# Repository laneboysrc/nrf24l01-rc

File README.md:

# nRF24-based RC car receiver, compatible with HobbyKing HK310 and Turnigy 3XS

This project includes **electronics** and **firmware** to build **surface RC receivers** that can replace the HobbyKing [HKR3000](http://hobbyking.com/hobbyking/store/__12187__HK_3000_3ch_2_4ghz_FHSS_RX_suit_the_HK310_Transmitter.html) and [XR3100](http://hobbyking.com/hobbyking/store/__22910__HK3100_3ch_2_4ghz_FHSS_Micro_RX_suits_HK310_Turnigy_3XS_TX_.html) receivers. They can be used with the [HK300](http://hobbyking.com/hobbyking/store/__12177__HK_300_3_Channel_2_4ghz_FHSS_Ground_Radio.html), [HK310](http://hobbyking.com/hobbyking/store/__12181__HK_310_3_Channel_2_4ghz_FHSS_Ground_Radio.html) and [Turnigy 3XS](http://hobbyking.com/hobbyking/store/__24905__Turnigy_3XS_FHSS_2_4GHz_3_Channel_Radio_System.html) RC car radio systems.

The receivers make use of off-the-shelf inexpensive RF modules.

Two variants are provided:

- [lpc812-nrf24l01](lpc812-nrf24l01-receiver/): NRF24L01+ module plus a [NXP LPC812](http://www.nxp.com/products/microcontrollers/cortex_m0_m0/series/LPC800.html) MCU
- [nrf24le1](nrf24le1-receiver/): Using a NRF24LE1 module (integrated 8051 MCU)

Technical information about the inner working of the receivers can be found
in **[hkr3000-info.md](doc/hkr3000-info.md)**.

## Advantages of the NRF24L01+ - LPC812 version

- Easily obtainable and very low cost NRF module (less than USD 1 including shipping in qty 10 on eBay, Aliexpress)
- Very precise servo pulses due to LPC812 timer hardware
- ARM Cortex-M0 32-bit CPU is easy to program for with the GCC ARM compiler
- No proprietary programmer required as the MCU has a ROM bootloader that can be flashed with an  USB-to-serial dongle
- Servo pulses can be updated down to every 5 ms (200 Hz). In theory this may provide better response but in practice the transmitter would need to be modified to fully take
advantage of this fact.
- UART output using the LANE Boys RC [preprocessor protocol](http://laneboysrc.blogspot.com/2012/12/pre-processor-for-diy-rc-light.html), e.g. to hook up the [DIY RC light controller](https://github.com/laneboysrc/rc-light-controller) with a single servo cable.

Downsides:

- Requires a PCB and intermediate SMD soldering skills
- No CPPM output (but it has a UART output that can carry CPPM-like data and more)

## Advantages of the NRF24LE1 version

- Low part count: NRF24LE1 module, voltage regulator, a few capacitors; done!
- Simple to build even on a breadboard
- CPPM output
- UART output using the LANE Boys RC [preprocessor protocol](http://laneboysrc.blogspot.com/2012/12/pre-processor-for-diy-rc-light.html), e.g. to hook up the [DIY RC light controller](https://github.com/laneboysrc/rc-light-controller) with a single servo cable. Baudrate is limited to 38400 though.

Downsides:

- NRF24LE1 module is more expensive than NRF24L01 and harder to find
- Requires special programming hardware. Multiple open-source versions can be found on the Internet.
- Servo pulses are software timed, hence slightly jittery despite using interrupts. Note that the firmware included in this project is improved over the original HKR3000 and XR3100 firmware, which regularly extends servo pulses by 16 us due to poor interrupt logic implementation.
- For the PCB provided in this project you need to get the NRF24LE1 module version that has an SMD crystal (size 21 x 15 mm)

The NRF24LE1 firmware included in this project can be compiled to be compatible with the HKR3000 and XR3100 hardware. However, since those receivers use the OTP version (NRF24LE1G) one would have to replace the chip with the NR24LE1E versions to be able to use it.

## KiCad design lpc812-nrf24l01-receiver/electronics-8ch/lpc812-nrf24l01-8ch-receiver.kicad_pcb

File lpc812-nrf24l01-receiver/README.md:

The LPC812-based receiver comes in two variants:

3/4 channel version
- Supports the original HobbyKing HK310 protocol
- Supports the LANE Boys RC 4 channel protocol
- Based on 16 pin TSSOP LPC812
- Uses the cheap nRF24 modules with the 2x4 pinheader

8 channel version
- Supports the original HobbyKing HK310 protocol
- Supports the LANE Boys RC 4 channel protocol
- Supports the LANE Boys RC 8 channel protocol
- Based on 20 pin TSSOP LPC812
- Uses a different, smaller nRF24L01 module that comes variants
with PCB antenna and IPX connector

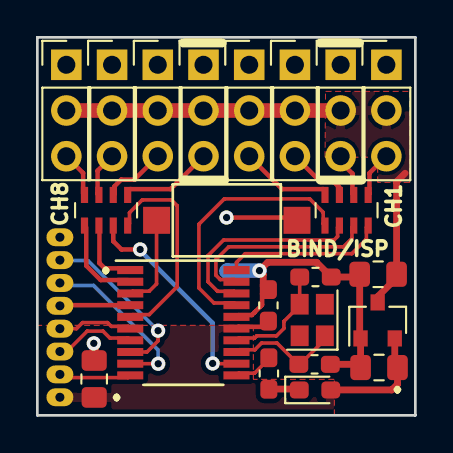
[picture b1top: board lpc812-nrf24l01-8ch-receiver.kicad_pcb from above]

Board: 2 copper layers, 21.0 x 21.0 mm, 23 parts (1 on the bottom side), 30 nets.

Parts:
C1: 1u/16V; C_0805_2012Metric_Pad1.15x1.40mm_HandSolder
C3, C5: 47u/6.3V; C_0805_2012Metric_Pad1.15x1.40mm_HandSolder
C4: 100n; C_0603_1608Metric_Pad1.05x0.95mm_HandSolder
C6, C7: 18p; C_0603_1608Metric_Pad1.05x0.95mm_HandSolder
D1: LED; LED_0603_1608Metric_Pad1.05x0.95mm_HandSolder
J1: CH1; PinHeader_1x03_P2.54mm_Vertical
J2: CH2/Rx; PinHeader_1x03_P2.54mm_Vertical
J3: CH3; PinHeader_1x03_P2.54mm_Vertical
J4: CH4; PinHeader_1x03_P2.54mm_Vertical
J5: CH5/Tx; PinHeader_1x03_P2.54mm_Vertical
J6: CH6; PinHeader_1x03_P2.54mm_Vertical
J7: CH7; PinHeader_1x03_P2.54mm_Vertical
J8: CH8; PinHeader_1x03_P2.54mm_Vertical
R1: 270; R_0603_1608Metric_Pad1.05x0.95mm_HandSolder
RN1, RN2: 1k x 4; R_Array_Concave_4x0603
SW1: BIND/ISP; Tact switch 6x4x3
U1: MCP1703A-3302_SOT23; SOT-23
U2: LPC812M101JDH20; TSSOP-20_4.4x6.5mm_P0.65mm
U3: NRF24L01_E01_ML01; nrf24l01-E01-ML01IPX
Y1: 12MHz; Crystal_SMD_2520-4Pin_2.5x2.0mm

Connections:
/BIND-ISP: SW1.1, U2.3
/CE: U2.10, U3.2
/CH1: RN1.4, U2.20
/CH2-Rx: RN1.3, U2.19
/CH3: RN1.2, U2.18
/CH4: RN1.1, U2.17
/CH5-Tx: RN2.4, U2.5
/CH6: RN2.3, U2.12
/CH7: RN2.2, U2.1
/CH8: RN2.1, U2.2
/CSN: U2.7, U3.3
/IRQ: U2.8, U3.7
/LED: R1.2, U2.11
/MISO: U2.9, U3.6
/MOSI: U2.4, U3.5
/SCK: U2.6, U3.4
/XTALIN: C7.1, U2.14, Y1.3
/XTALOUT: C6.1, U2.13, Y1.1
GND: C1.2, C3.2, C4.2, C5.2, C6.2, C7.2, J1.1, J2.1, J3.1, J4.1, J5.1, J6.1, J7.1, J8.1, SW1.2, U1.1, U2.16, U3.8
unnamed: D1.1, R1.1
unnamed: J1.3, RN1.5
unnamed: J2.3, RN1.6
unnamed: J3.3, RN1.7
unnamed: J4.3, RN1.8
unnamed: J5.3, RN2.5
unnamed: J6.3, RN2.6
unnamed: J7.3, RN2.7
unnamed: J8.3, RN2.8
VCC: C3.1, C4.1, C5.1, D1.2, U1.2, U2.15, U3.1
VDD: C1.1, J1.2, J2.2, J3.2, J4.2, J5.2, J6.2, J7.2, J8.2, U1.3

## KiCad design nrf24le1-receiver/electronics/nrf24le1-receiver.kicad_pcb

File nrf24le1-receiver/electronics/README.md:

# Schematics and PCB layout for the NRF24LE1 receiver

The source files are for [Kicad](http://www.kicad-pcb.org).

For convenience the [schematics](SCHEMATICS.pdf) are also available as PDF.

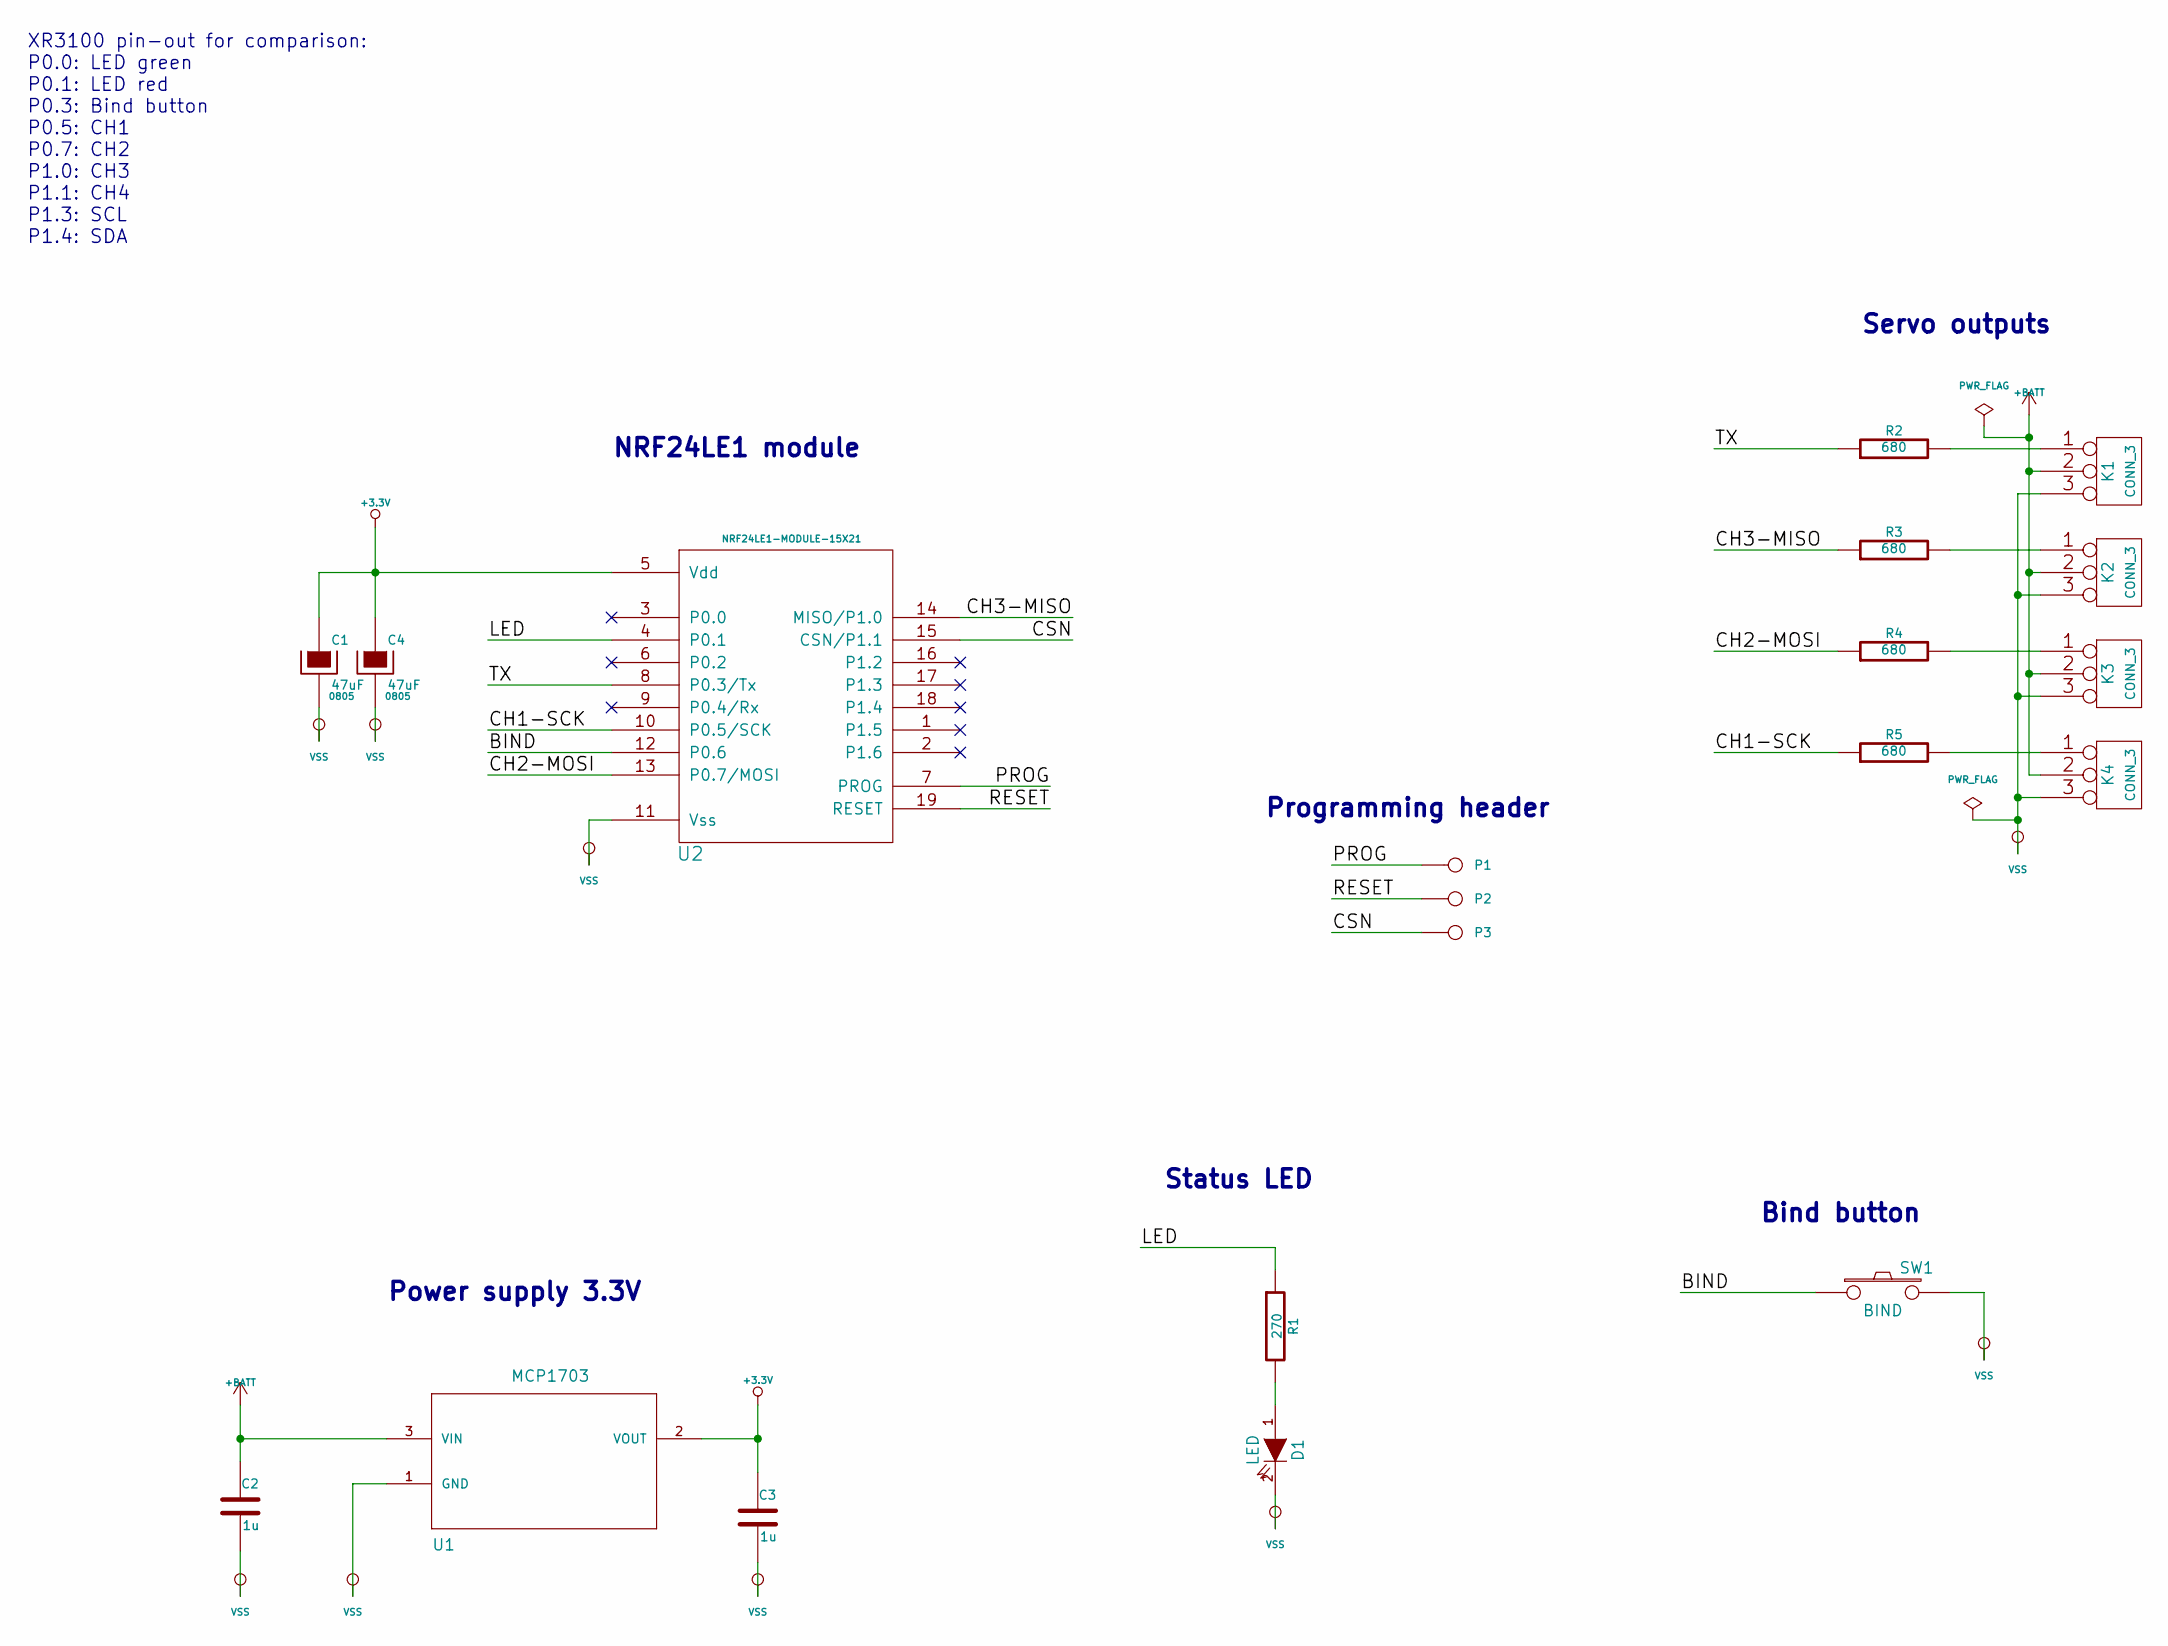
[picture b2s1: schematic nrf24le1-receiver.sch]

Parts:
C1, C4: 47uF; 0805
C2, C3: 1u
D1: LED
K1, K2, K3, K4: CONN_3
P1, P2, P3: CONN_1
R1: 270
R2, R3, R4, R5: 680
SW1: BIND
U1: MCP1703; MCP1703-SOT95P300X145-3N
U2: NRF24LE1-MODULE-15X21

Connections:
+3.3V: C1.1, C3.1, C4.1, U1.2 (VOUT), U2.5 (Vdd)
+BATT: C2.1, K1.2 (PM), K2.2 (PM), K3.2 (PM), K4.2 (PM), U1.3 (VIN)
/BIND: SW1.1, U2.12 (P0.6)
/CH1-SCK: R5.1, U2.10 (P0.5/SCK)
/CH2-MOSI: R4.1, U2.13 (P0.7/MOSI)
/CH3-MISO: R3.1, U2.14 (MISO/P1.0)
/CSN: P3.1, U2.15 (CSN/P1.1)
/LED: R1.1, U2.4 (P0.1)
/PROG: P1.1, U2.7 (PROG)
/RESET: P2.1, U2.19 (RESET)
/TX: R2.1, U2.8 (P0.3/Tx)
unnamed: K4.1, R5.2
unnamed: K1.1, R2.2
unnamed: K2.1, R3.2
unnamed: K3.1, R4.2
unnamed: D1.1 (A), R1.2
VSS: C1.2, C2.2, C3.2, C4.2, D1.2 (K), K1.3, K2.3, K3.3, K4.3, SW1.2, U1.1 (GND), U2.11 (Vss)

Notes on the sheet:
XR3100 pin-out for comparison: P0.0: LED green P0.1: LED red P0.3: Bind button P0.5: CH1 P0.7: CH2 P1.0: CH3 P1.1: CH4 P1.3: SCL P1.4: SDA
NRF24LE1 module
Programming header
Servo outputs
Status LED
Power supply 3.3V
Bind button

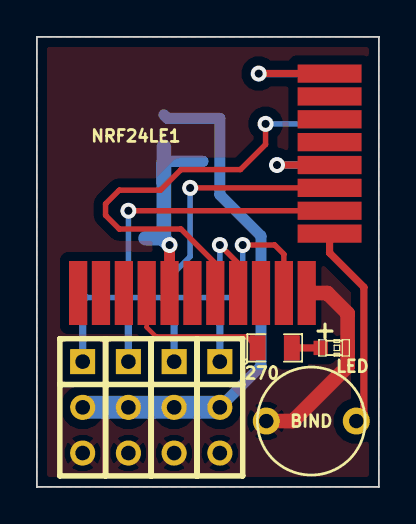
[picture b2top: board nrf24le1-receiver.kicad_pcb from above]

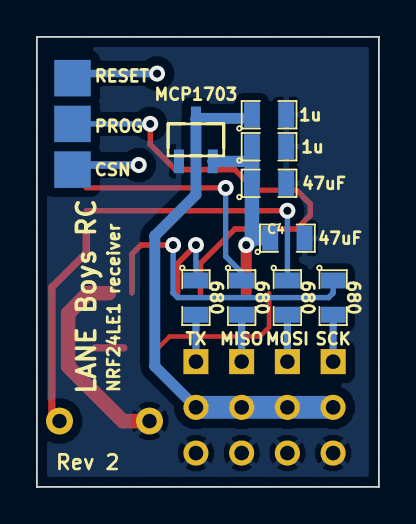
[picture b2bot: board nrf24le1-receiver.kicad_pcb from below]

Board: 2 copper layers, 19.0 x 25.0 mm, 20 parts (12 on the bottom side), 17 nets.

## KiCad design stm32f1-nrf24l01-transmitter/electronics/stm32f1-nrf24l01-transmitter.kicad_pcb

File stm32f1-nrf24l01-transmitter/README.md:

# STM32F103 and NRF24L01+ based headless transmitter

This project implements a 2.4 GHz RC transmitter using the NRF24L01+ wireless module and the STM32F103C8T6 module. It runs of a 1S Li-Ion battery.

The transmitter is designed to be used in old RC transmitter hardware, or to turn a cheap RC simulator transmitter into a fully operational RC transmitter. As such it is designed for headless operation. Setup is carried out via a wirelessly connected programming box.

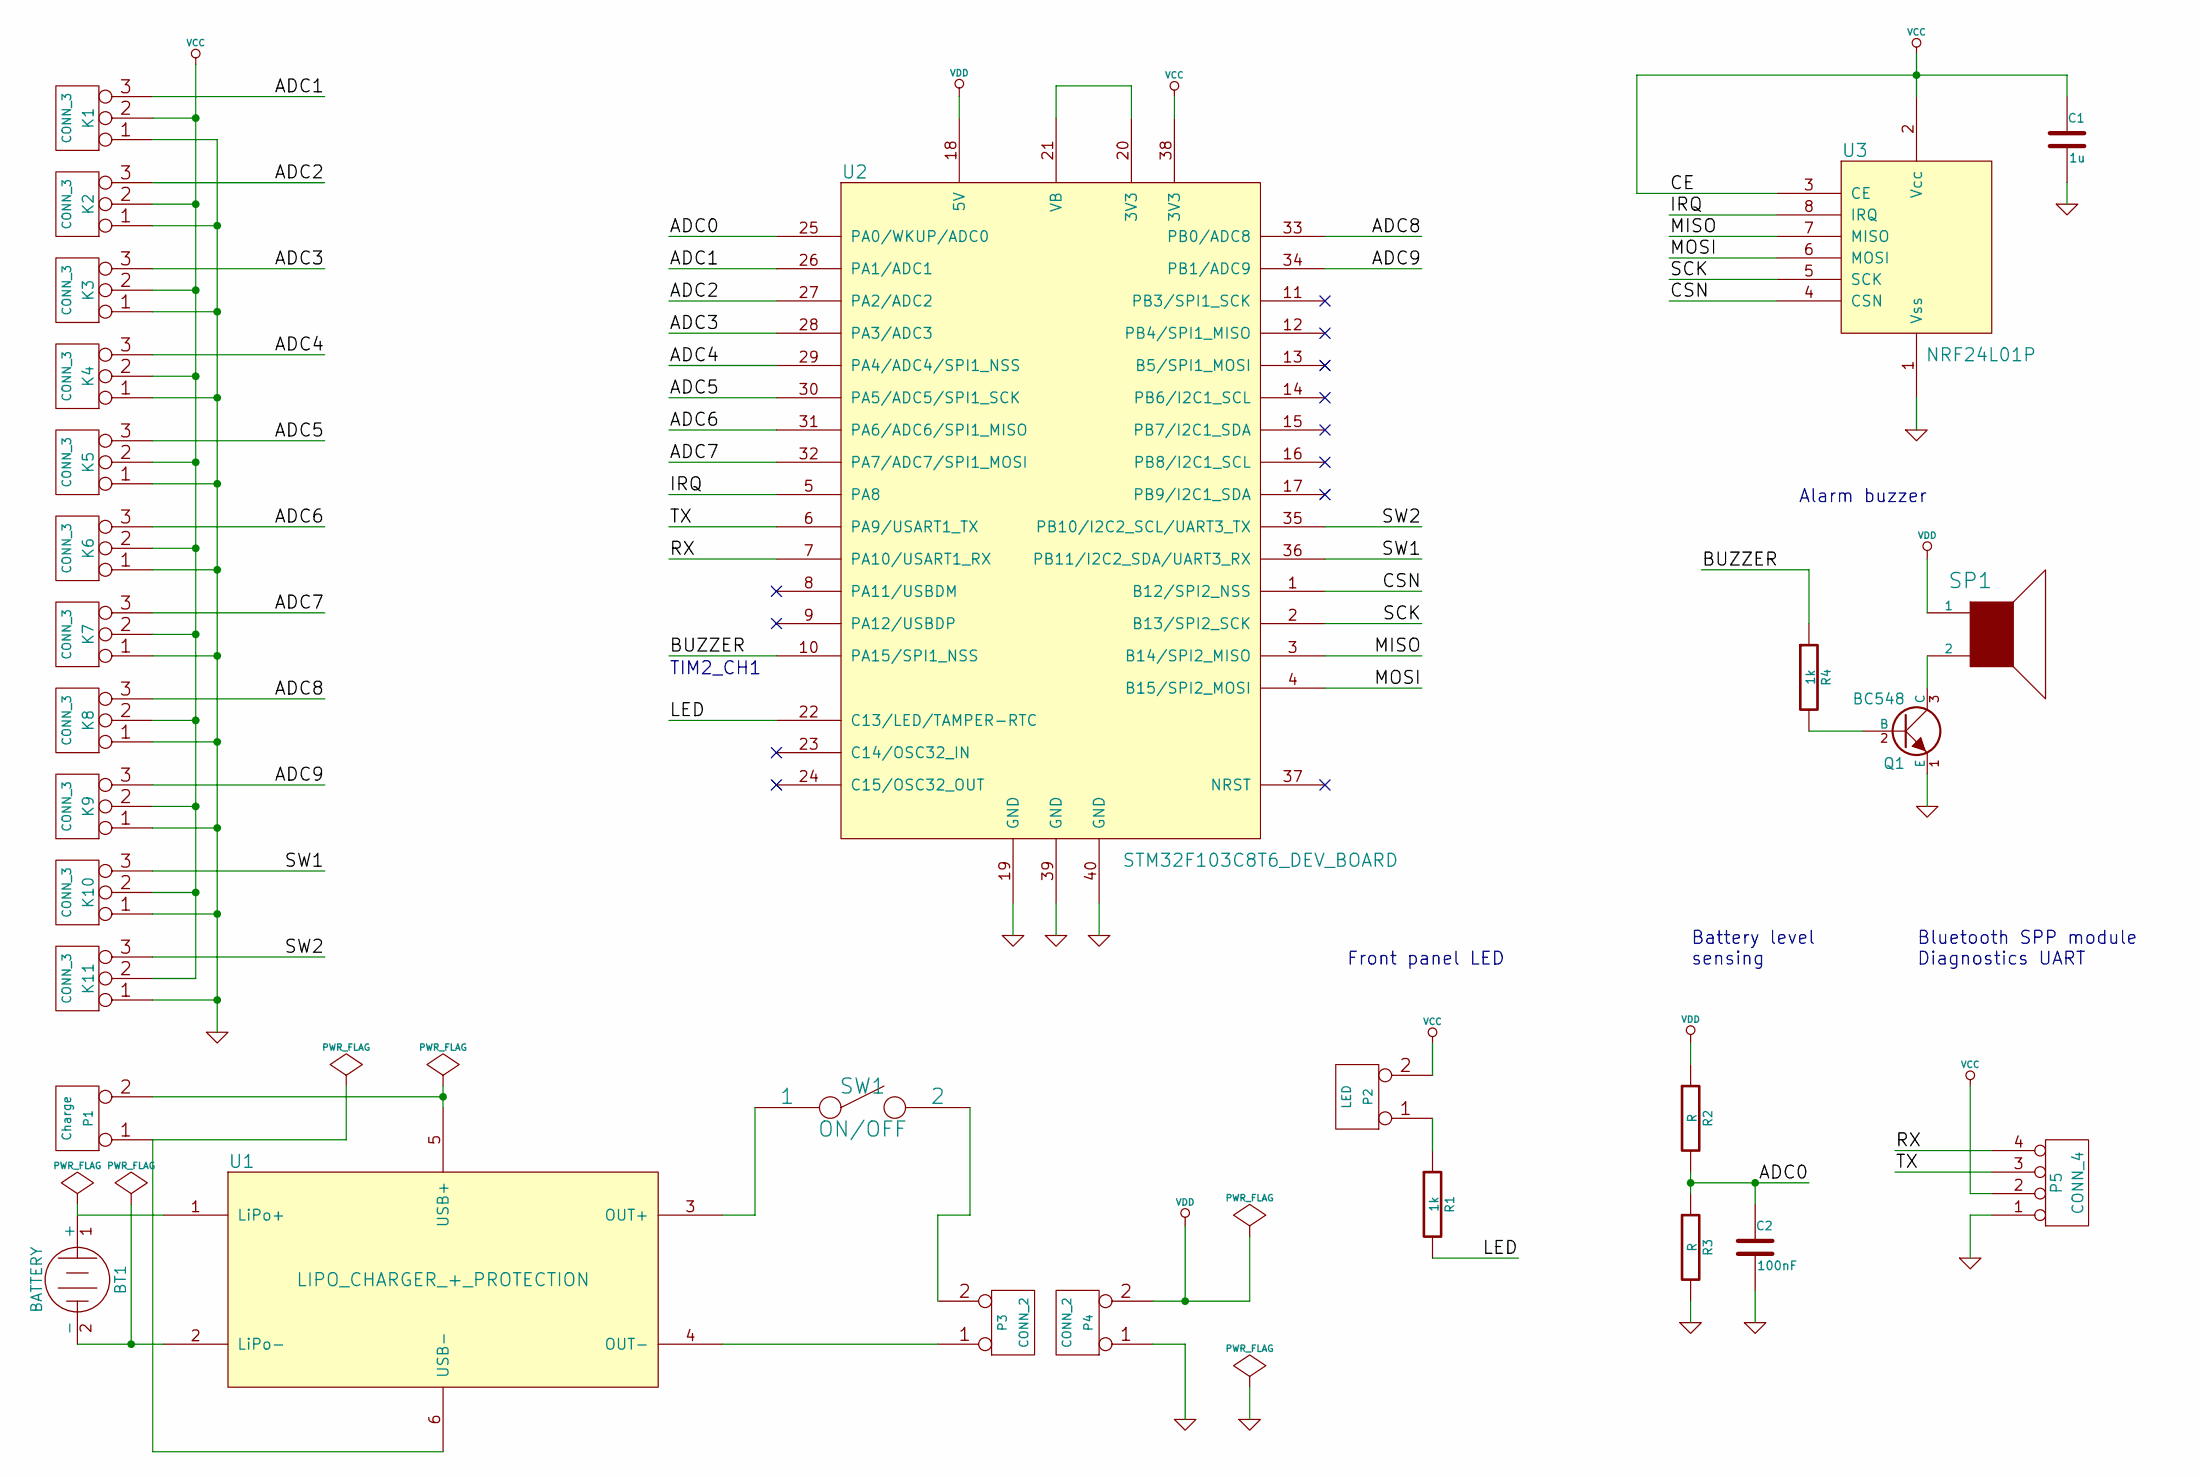
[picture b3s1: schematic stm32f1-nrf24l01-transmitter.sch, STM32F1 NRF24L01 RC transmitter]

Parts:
BT1: BATTERY
C1: 1u
C2: 100nF
K1, K2, K3, K4, K5, K6, K7, K8, K9, K10, K11: CONN_3
P1: Charge
P2: LED
P3, P4: CONN_2
P5: CONN_4
Q1: BC548
R1, R4: 1k
R2, R3: R
SP1: SPEAKER
SW1: ON/OFF
U1: LIPO_CHARGER_+_PROTECTION
U2: STM32F103C8T6_DEV_BOARD
U3: NRF24L01P

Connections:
/ADC0: C2.1, R2.2, R3.1, U2.25 (PA0/WKUP/ADC0)
/ADC1: K1.3, U2.26 (PA1/ADC1)
/ADC2: K2.3, U2.27 (PA2/ADC2)
/ADC3: K3.3, U2.28 (PA3/ADC3)
/ADC4: K4.3, U2.29 (PA4/ADC4/SPI1_NSS)
/ADC5: K5.3, U2.30 (PA5/ADC5/SPI1_SCK)
/ADC6: K6.3, U2.31 (PA6/ADC6/SPI1_MISO)
/ADC7: K7.3, U2.32 (PA7/ADC7/SPI1_MOSI)
/ADC8: K8.3, U2.33 (PB0/ADC8)
/ADC9: K9.3, U2.34 (PB1/ADC9)
/BUZZER: R4.1, U2.10 (PA15/SPI1_NSS)
/CSN: U2.1 (B12/SPI2_NSS), U3.4 (CSN)
/IRQ: U2.5 (PA8), U3.8 (IRQ)
/LED: R1.2, U2.22 (C13/LED/TAMPER-RTC)
/MISO: U2.3 (B14/SPI2_MISO), U3.7 (MISO)
/MOSI: U2.4 (B15/SPI2_MOSI), U3.6 (MOSI)
/RX: P5.4, U2.7 (PA10/USART1_RX)
/SCK: U2.2 (B13/SPI2_SCK), U3.5 (SCK)
/SW1: K10.3, U2.36 (PB11/I2C2_SDA/UART3_RX)
/SW2: K11.3, U2.35 (PB10/I2C2_SCL/UART3_TX)
/TX: P5.3, U2.6 (PA9/USART1_TX)
GND: C1.2, C2.2, K1.1, K2.1, K3.1, K4.1, K5.1, K6.1, K7.1, K8.1, K9.1, K10.1, K11.1, P4.1, P5.1, Q1.1 (E), R3.2, U2.19 (GND), U2.39 (GND), U2.40 (GND), U3.1 (Vss)
unnamed: BT1.1 (+), U1.1 (LiPo+)
unnamed: BT1.2 (-), U1.2 (LiPo-)
unnamed: P1.2 (PM), U1.5 (USB+)
unnamed: Q1.2 (B), R4.2
unnamed: Q1.3 (C), SP1.2
unnamed: P1.1, U1.6 (USB-)
unnamed: U2.20 (3V3), U2.21 (VB)
unnamed: P3.2 (PM), SW1.2
unnamed: P3.1, U1.4 (OUT-)
unnamed: SW1.1, U1.3 (OUT+)
unnamed: P2.1, R1.1
VCC: C1.1, K1.2 (PM), K2.2 (PM), K3.2 (PM), K4.2 (PM), K5.2 (PM), K6.2 (PM), K7.2 (PM), K8.2 (PM), K9.2 (PM), K10.2 (PM), K11.2 (PM), P2.2 (PM), P5.2, U2.38 (3V3), U3.2 (Vcc), U3.3 (CE)
VDD: P4.2 (PM), R2.1, SP1.1, U2.18 (5V)

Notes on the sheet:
Battery level sensing
Bluetooth SPP module Diagnostics UART
Front panel LED
Alarm buzzer
TIM2_CH1

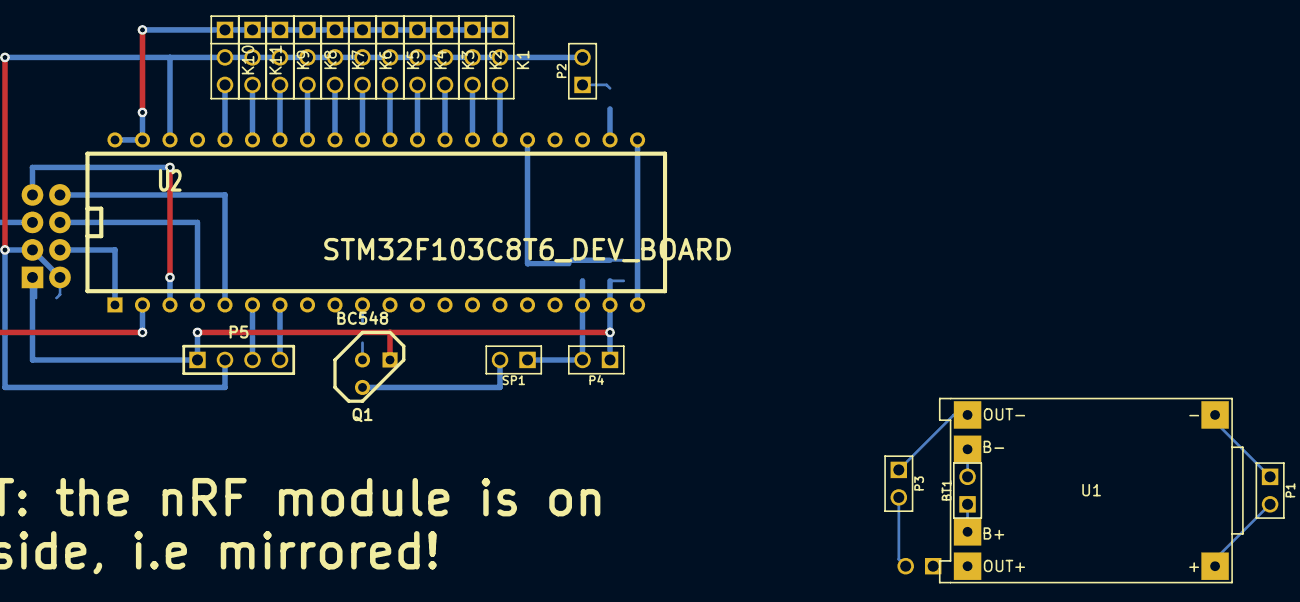
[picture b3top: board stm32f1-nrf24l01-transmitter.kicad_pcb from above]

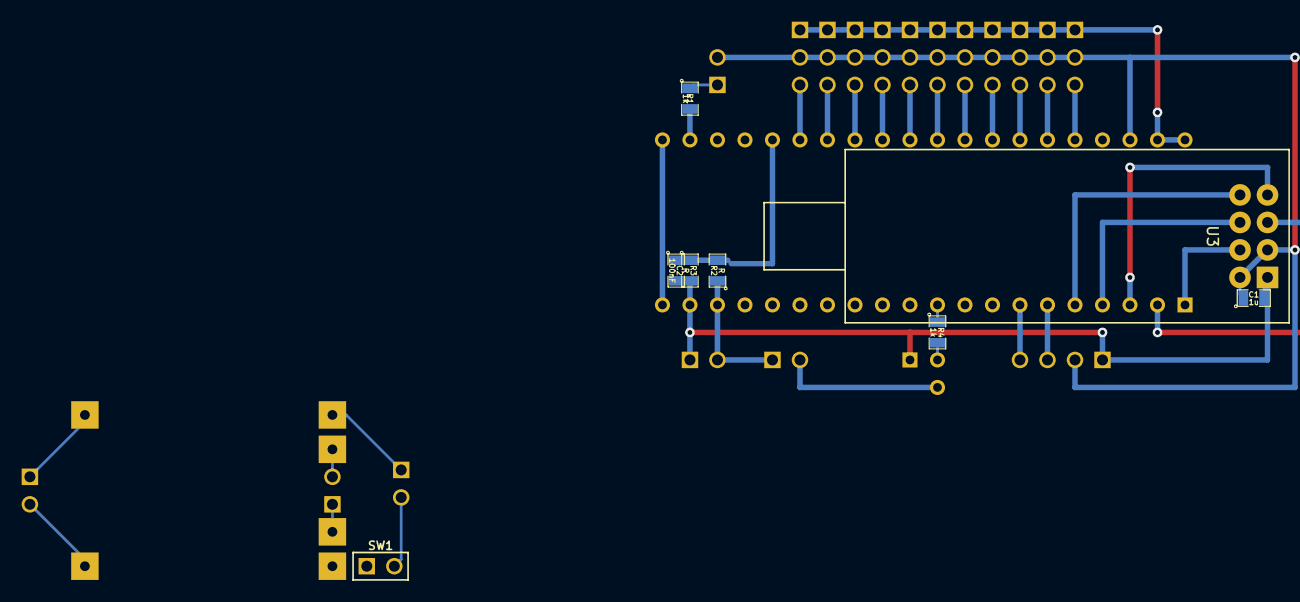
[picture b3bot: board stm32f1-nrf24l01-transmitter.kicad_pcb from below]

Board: 2 copper layers, 29 parts (8 on the bottom side), 35 nets.

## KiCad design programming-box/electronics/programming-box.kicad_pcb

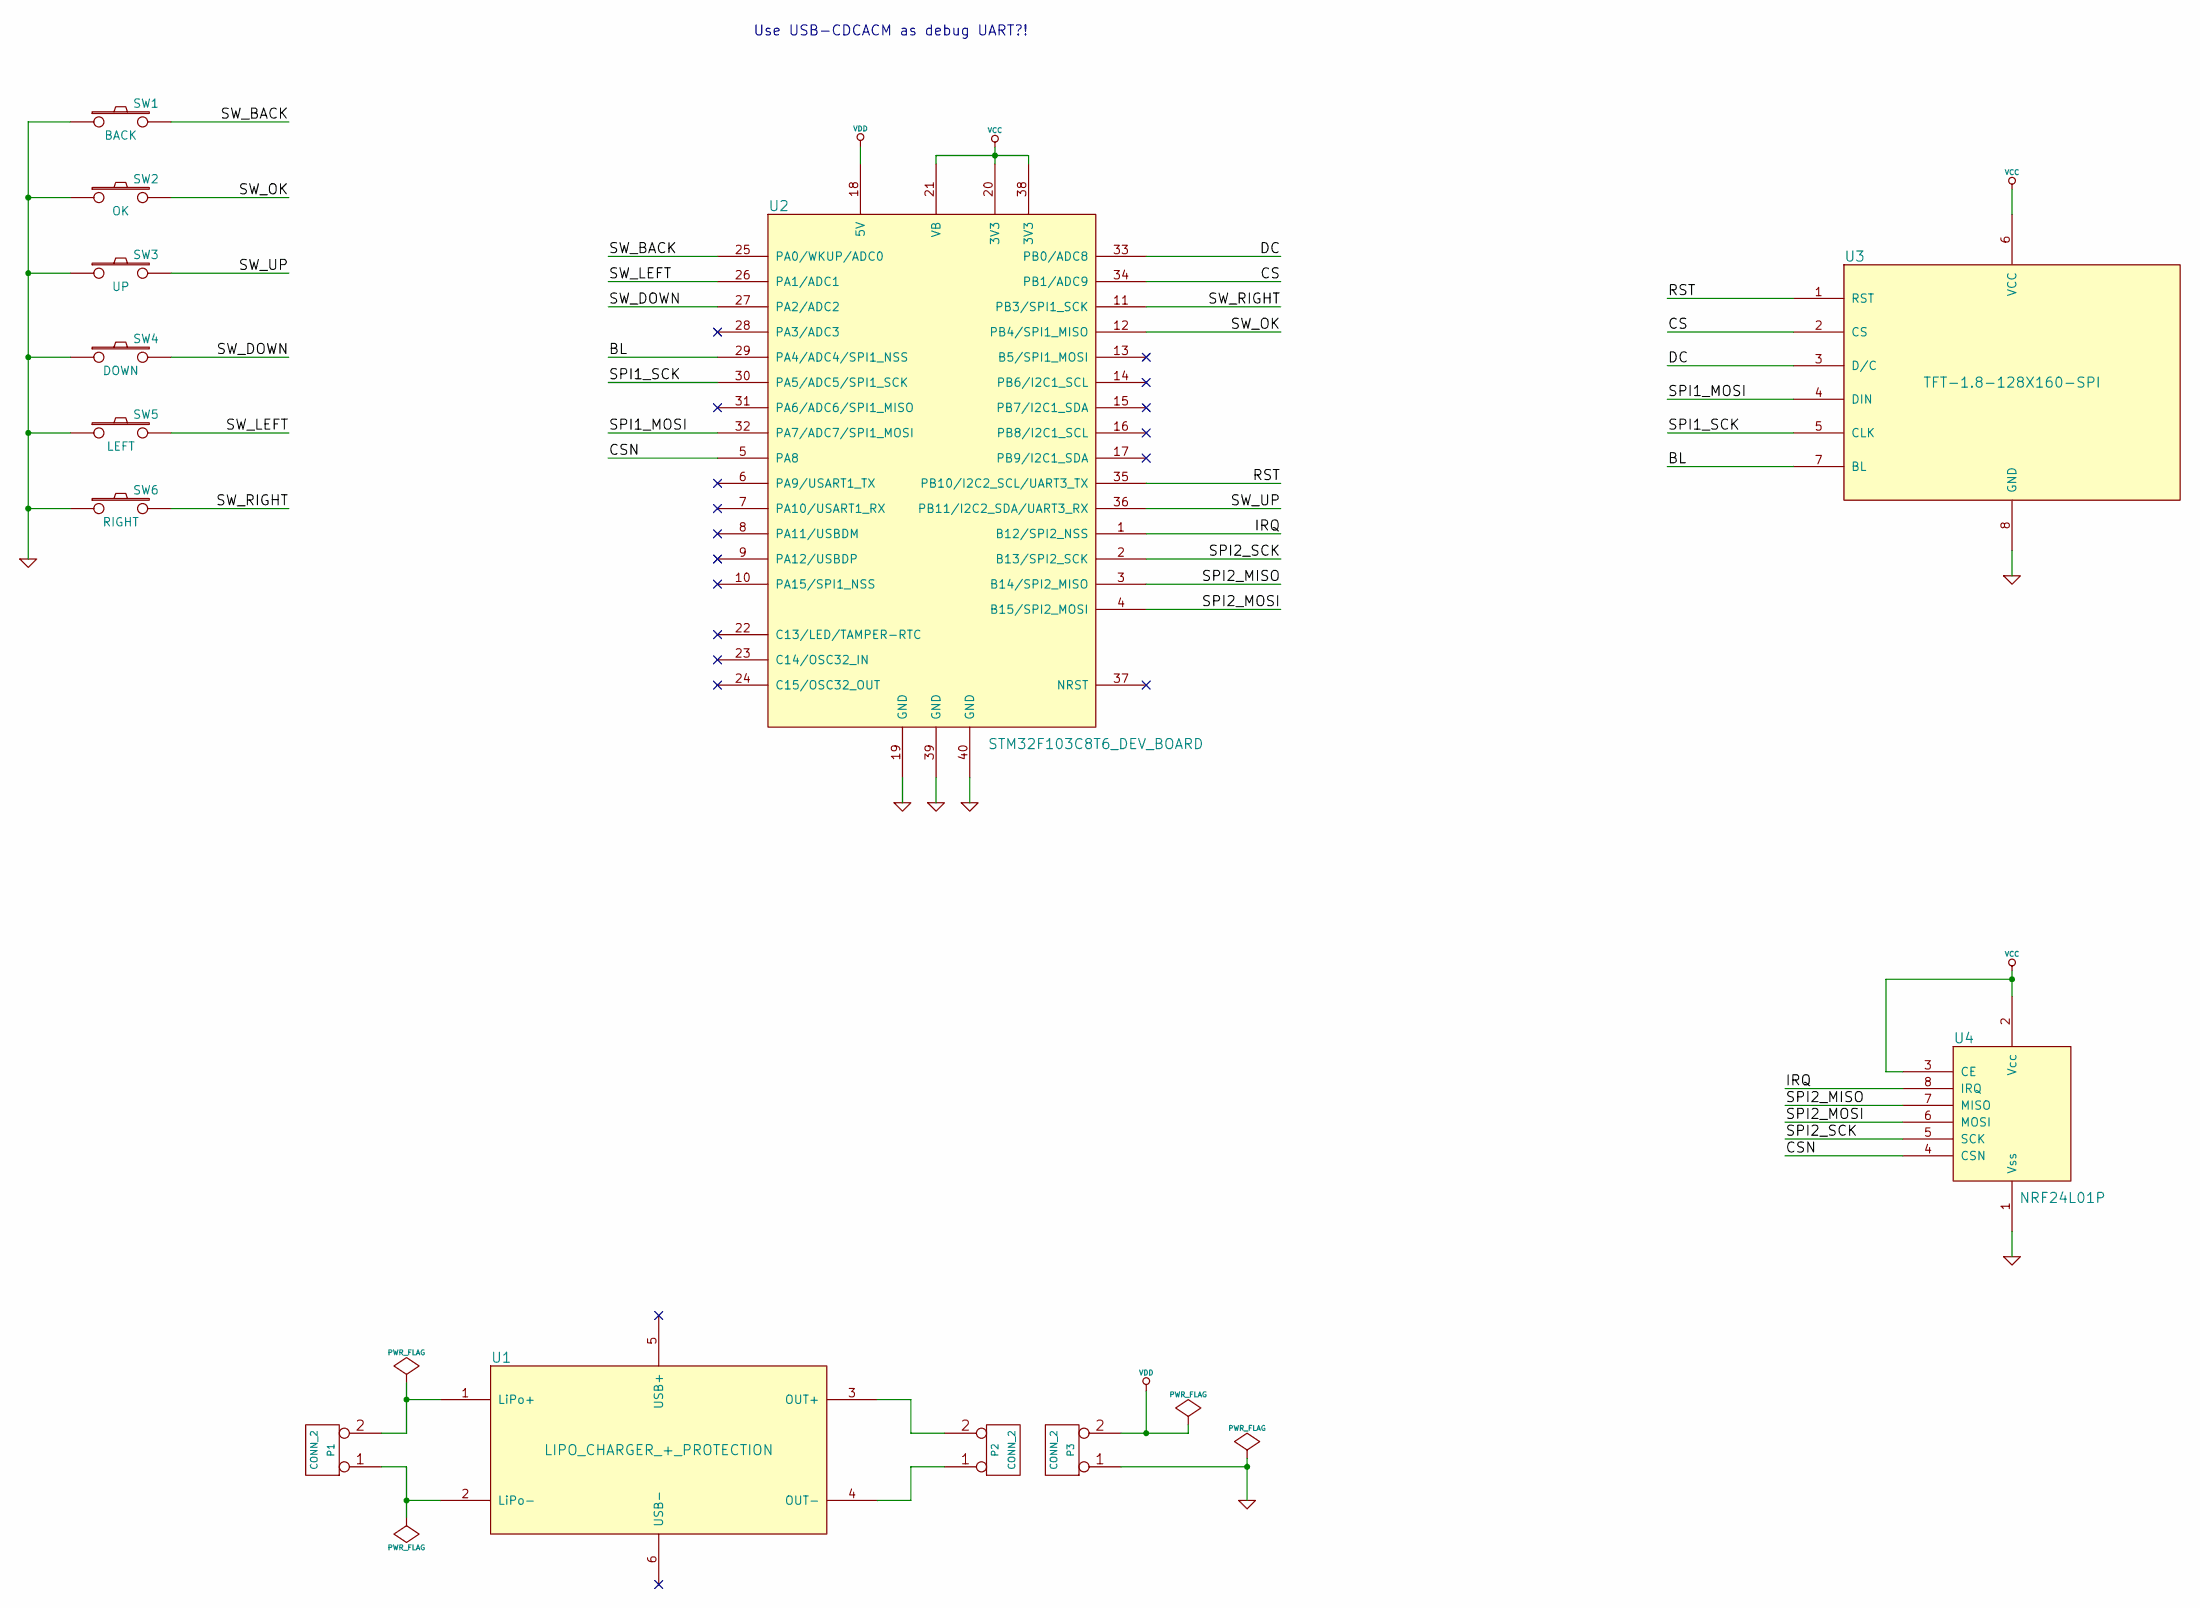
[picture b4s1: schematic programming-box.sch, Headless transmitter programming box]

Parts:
P1, P2, P3: CONN_2
SW1: BACK
SW2: OK
SW3: UP
SW4: DOWN
SW5: LEFT
SW6: RIGHT
U1: LIPO_CHARGER_+_PROTECTION
U2: STM32F103C8T6_DEV_BOARD
U3: TFT-1.8-128X160-SPI
U4: NRF24L01P

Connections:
/BL: U2.29 (PA4/ADC4/SPI1_NSS), U3.7 (BL)
/CS: U2.34 (PB1/ADC9), U3.2 (CS)
/CSN: U2.5 (PA8), U4.4 (CSN)
/DC: U2.33 (PB0/ADC8), U3.3 (D/C)
/IRQ: U2.1 (B12/SPI2_NSS), U4.8 (IRQ)
/RST: U2.35 (PB10/I2C2_SCL/UART3_TX), U3.1 (RST)
/SPI1_MOSI: U2.32 (PA7/ADC7/SPI1_MOSI), U3.4 (DIN)
/SPI1_SCK: U2.30 (PA5/ADC5/SPI1_SCK), U3.5 (CLK)
/SPI2_MISO: U2.3 (B14/SPI2_MISO), U4.7 (MISO)
/SPI2_MOSI: U2.4 (B15/SPI2_MOSI), U4.6 (MOSI)
/SPI2_SCK: U2.2 (B13/SPI2_SCK), U4.5 (SCK)
/SW_BACK: SW1.2, U2.25 (PA0/WKUP/ADC0)
/SW_DOWN: SW4.2, U2.27 (PA2/ADC2)
/SW_LEFT: SW5.2, U2.26 (PA1/ADC1)
/SW_OK: SW2.2, U2.12 (PB4/SPI1_MISO)
/SW_RIGHT: SW6.2, U2.11 (PB3/SPI1_SCK)
/SW_UP: SW3.2, U2.36 (PB11/I2C2_SDA/UART3_RX)
GND: P3.1, SW1.1, SW2.1, SW3.1, SW4.1, SW5.1, SW6.1, U2.19 (GND), U2.39 (GND), U2.40 (GND), U3.8 (GND), U4.1 (Vss)
unnamed: P1.2 (PM), U1.1 (LiPo+)
unnamed: P1.1, U1.2 (LiPo-)
unnamed: P2.2 (PM), U1.3 (OUT+)
unnamed: P2.1, U1.4 (OUT-)
VCC: U2.20 (3V3), U2.21 (VB), U2.38 (3V3), U3.6 (VCC), U4.2 (Vcc), U4.3 (CE)
VDD: P3.2 (PM), U2.18 (5V)

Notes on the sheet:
Use USB-CDCACM as debug UART?!

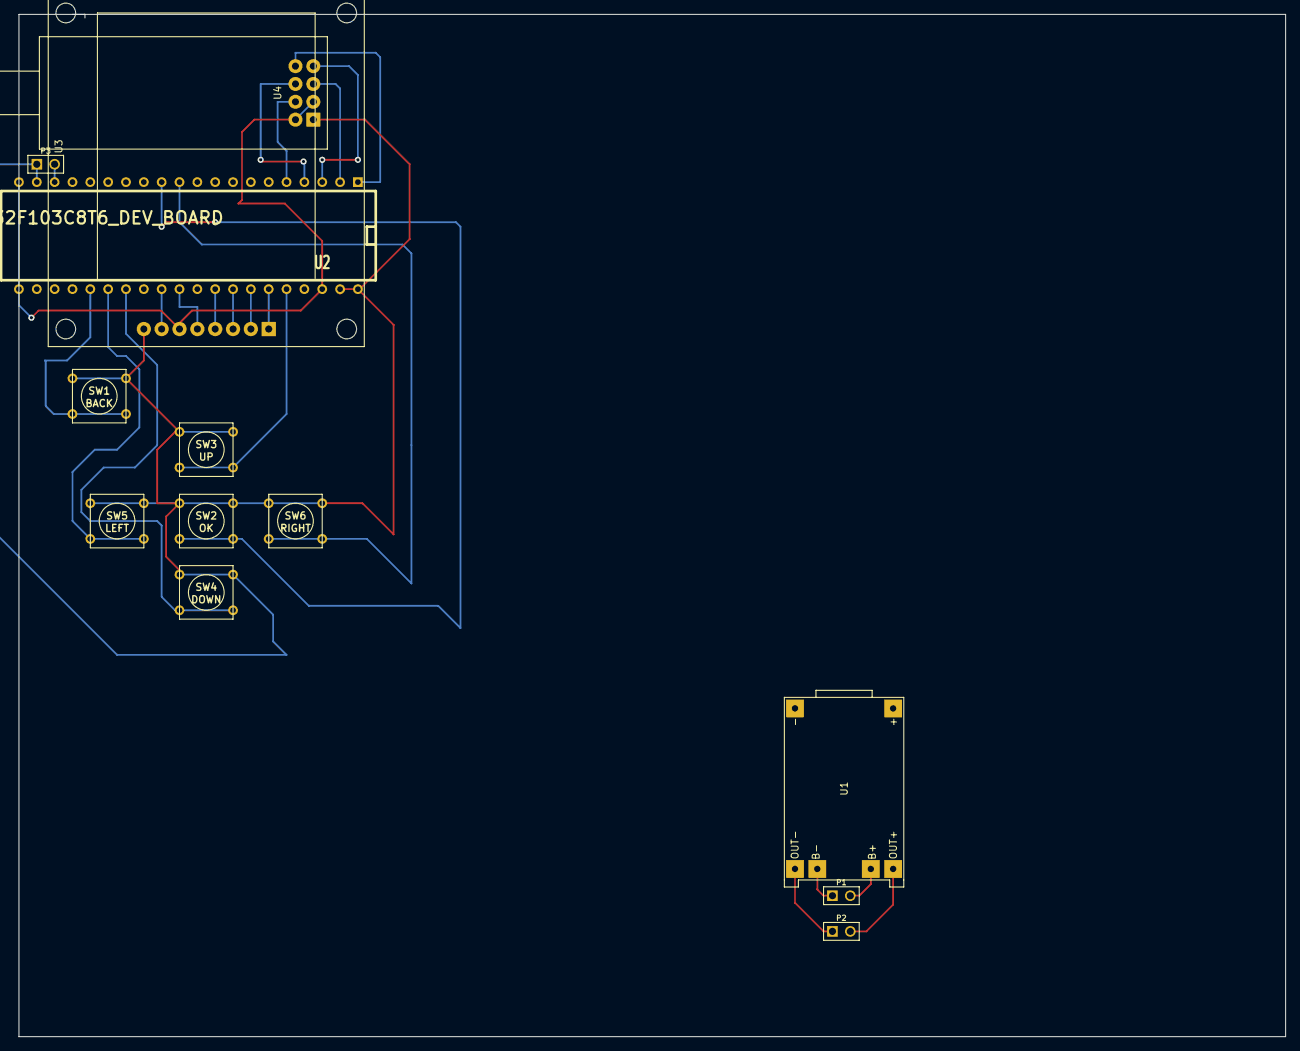
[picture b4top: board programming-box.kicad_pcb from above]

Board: 2 copper layers, 180.3 x 145.5 mm, 13 parts (0 on the bottom side), 24 nets.
